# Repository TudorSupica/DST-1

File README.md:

# The [BOSS DS-1](https://www.thomann.de/ro/boss_ds1_distortion.htm)

Maybe the most popular distortion pedal to ever hit the market. It's harsh attack and heavy distortion make it the perfect choice for genres like thrash and heavy metal.

# The [DST-1](https://github.com/TudorSupica/DST-1/)

The DST-1 is a copy of the DS-1's schematic, but modified in certain ways.
The original DS-1 used some relatively hard to find components, so i've swapped those out with some common components like the 2N3904 and the TL072.

This distorion pedal is intended to set the standard to me as to what "a good distortion pedal" sounds like. Usually distortion pedals are quite cheap and easy to build, but their sound comes down to the components used. Thus, I might swap out the TL072 for other op-amps aswell as the transistors. Good components make good pedals, but sometimes their cheapness and imperfections make the pedal unique. 

# [The Schematic](https://github.com/TudorSupica/DST-1/blob/main/Schematic/)

The schematic is quite cramped since I wanted it to fit all in a single unbroken signal line, from the input to the output. The +Vcc and -Vcc are supplied using a voltage divider between the positive and negative terminals of a 9v battery, also forming a vitual ground. To make sure I make the disctinction between the Gnd of the battery and the Gnd of the signal, I decided to rename signal's ground to +4,5v since it's the midway point between the +9v and the 0v of the battery.

The 3PDT switch didn't had any symbol in KiCAD's library so I made them myself, aswell as the footprint, using the datasheet for the switch. Feel free to copy use and share since resources should not be kept behind paywalls and such and anybody should have the right to use resources to create / recreate things.

# [The PCB](https://github.com/TudorSupica/DST-1/blob/main/PCB/)
I've yet to test the circuit, but the PCB is on it's way and will soonly arrive.

The PCB is made to fit in a Hammond 1590B aluminium enclosure, thus it's rather strict dimensions. I'm not quite sure if it'll fit tho since I've been too lazy to make the board's outline match the enclosure's lid, but I plan to do it... sometime in the future I hope ...

Here is the datasheet for the enclosure tho!

I also added some (4 to be precise) M3 mounting holes that are connected directly to 0v, thus being capable to ground the whole PCB if the user so desires.
The LED can be anything from red to UV, I used a 220 ohm resistor but it can be replaced with any kind of THT resistor to match the desired brightness/current need of an LED, if so desired.

I plan to power up the pedal using a 9v battery connected via a barrel jack, at the back of the board. 

To do:
- [x] Schematic
- [x] PCB design
- [ ] Integrate the pedal in an enclosure

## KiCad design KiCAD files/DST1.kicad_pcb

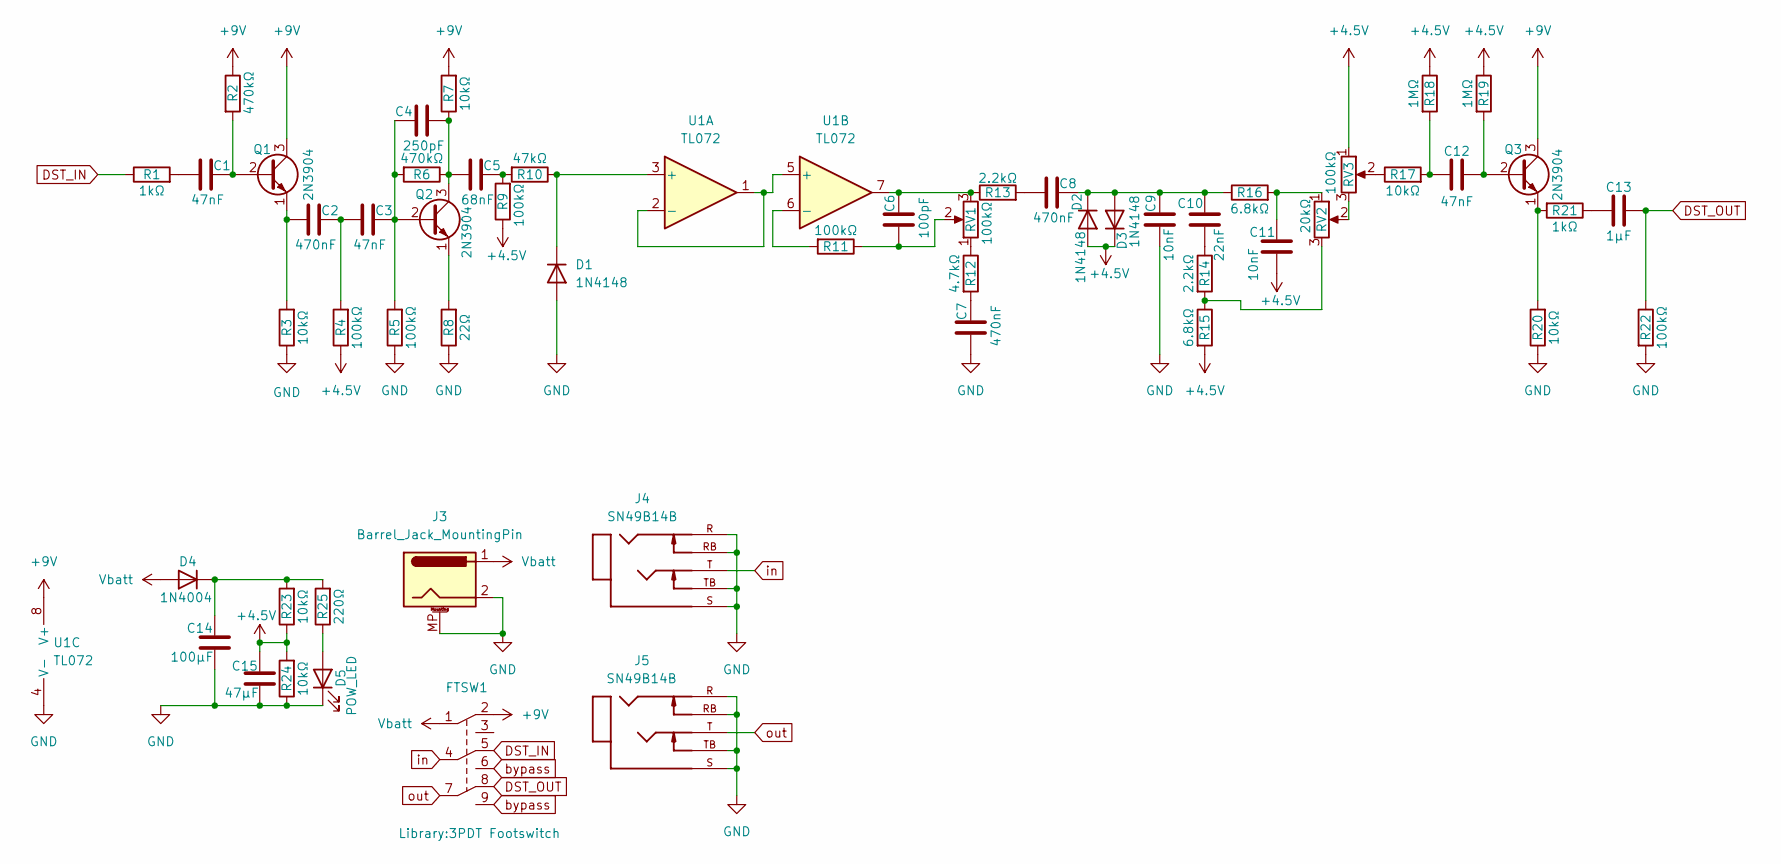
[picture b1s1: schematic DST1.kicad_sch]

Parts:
C1, C3, C12: 47nF; C_Rect_L4.6mm_W3.0mm_P2.50mm_MKS02_FKP02
C2, C7, C8: 470nF; C_Rect_L4.6mm_W3.0mm_P2.50mm_MKS02_FKP02
C4: 250pF; C_Rect_L4.6mm_W3.0mm_P2.50mm_MKS02_FKP02
C5: 68nF; C_Rect_L4.6mm_W3.0mm_P2.50mm_MKS02_FKP02
C6: 100pF; C_Rect_L4.6mm_W3.0mm_P2.50mm_MKS02_FKP02
C9, C11: 10nF; C_Rect_L4.6mm_W3.0mm_P2.50mm_MKS02_FKP02
C10: 22nF; C_Rect_L4.6mm_W3.0mm_P2.50mm_MKS02_FKP02
C13: 1µF; C_Rect_L4.6mm_W3.0mm_P2.50mm_MKS02_FKP02
C14: 100µF; C_Radial_D4.0mm_H5.0mm_P1.50mm
C15: 47µF; C_Radial_D4.0mm_H5.0mm_P1.50mm
D1, D2, D3: 1N4148; D_DO-35_SOD27_P7.62mm_Horizontal
D4: 1N4004; D_DO-41_SOD81_P10.16mm_Horizontal
D5: POW_LED; LED_D5.0mm
FTSW1: 3PDT Footswitch
J3: Barrel_Jack_MountingPin; BarrelJack_Kycon_KLDX-0202-xC_Horizontal
J4, J5: SN49B14B; PJ-644C; PARTREV F
Q1, Q2, Q3: 2N3904; TO-92
R1, R21: 1kΩ; R_Axial_DIN0207_L6.3mm_D2.5mm_P10.16mm_Horizontal
R2, R6: 470kΩ; R_Axial_DIN0207_L6.3mm_D2.5mm_P10.16mm_Horizontal
R3, R7, R17, R20, R23, R24: 10kΩ; R_Axial_DIN0207_L6.3mm_D2.5mm_P10.16mm_Horizontal
R4, R5, R9, R11, R22: 100kΩ; R_Axial_DIN0207_L6.3mm_D2.5mm_P10.16mm_Horizontal
R8: 22Ω; R_Axial_DIN0207_L6.3mm_D2.5mm_P10.16mm_Horizontal
R10: 47kΩ; R_Axial_DIN0207_L6.3mm_D2.5mm_P10.16mm_Horizontal
R12: 4.7kΩ; R_Axial_DIN0207_L6.3mm_D2.5mm_P10.16mm_Horizontal
R13, R14: 2.2kΩ; R_Axial_DIN0207_L6.3mm_D2.5mm_P10.16mm_Horizontal
R15, R16: 6.8kΩ; R_Axial_DIN0207_L6.3mm_D2.5mm_P10.16mm_Horizontal
R18, R19: 1MΩ; R_Axial_DIN0207_L6.3mm_D2.5mm_P10.16mm_Horizontal
R25: 220Ω; R_Axial_DIN0207_L6.3mm_D2.5mm_P10.16mm_Horizontal
RV1, RV3: 100kΩ; Potentiometer_Alpha_RD901F-40-00D_Single_Vertical
RV2: 20kΩ; Potentiometer_Alpha_RD901F-40-00D_Single_Vertical
U1: TL072; DIP-8_W7.62mm

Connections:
+4.5V: C11.1, C15.1, D2.2 (A), D3.1 (K), R4.1, R9.1, R15.2, R18.1, R19.1, R23.1, R24.2, RV3.1
+9V: FTSW1.2, Q1.3 (C), Q3.3 (C), R2.1, R7.2, U1.8 (V+)
DST_IN: FTSW1.5, R1.1
DST_OUT: C13.1, FTSW1.8, R22.1
GND: C7.1, C9.1, C14.2, C15.2, D1.2 (A), D5.1 (K), J3.2, J3.3, J3.MP (MountPin), J4.R, J4.RB, J4.S, J4.SB, J4.TB, J5.R, J5.RB, J5.S, J5.SB, J5.TB, R3.1, R5.1, R8.1, R20.1, R22.2, R24.1, U1.4 (V-)
unnamed: C1.1, R1.2
unnamed: C2.2, C3.1, R4.2
unnamed: C5.2, R9.2, R10.2
unnamed: C6.1, R11.1, RV1.2
unnamed: C6.2, R13.1, RV1.3, U1.7
unnamed: C7.2, R12.2
unnamed: C8.1, R13.2
unnamed: C10.1, R14.1
unnamed: C11.2, R16.2, RV2.1
unnamed: C12.2, R17.2, R18.2
unnamed: C13.2, R21.1
unnamed: D1.1 (K), R10.1, U1.3 (+)
unnamed: C8.2, C9.2, C10.2, D2.1 (K), D3.2 (A), R16.1
unnamed: C14.1, D4.1 (K), R23.2, R25.2
unnamed: D5.2 (A), R25.1
unnamed: C1.2, Q1.2 (B), R2.2
unnamed: C2.1, Q1.1 (E), R3.2
unnamed: C3.2, C4.1, Q2.2 (B), R5.2, R6.2
unnamed: C4.2, C5.1, Q2.3 (C), R6.1, R7.1
unnamed: Q2.1 (E), R8.2
unnamed: C12.1, Q3.2 (B), R19.2
unnamed: Q3.1 (E), R20.2, R21.2
unnamed: R12.1, RV1.1
unnamed: R14.2, R15.1, RV2.3
unnamed: R17.1, RV3.2
unnamed: RV2.2, RV3.3
unnamed: U1.1, U1.2 (-), U1.5 (+)
unnamed: R11.2, U1.6 (-)
Vbatt: D4.2 (A), FTSW1.1, J3.1
bypass: FTSW1.6, FTSW1.9
in: FTSW1.4, J4.T
out: FTSW1.7, J5.T

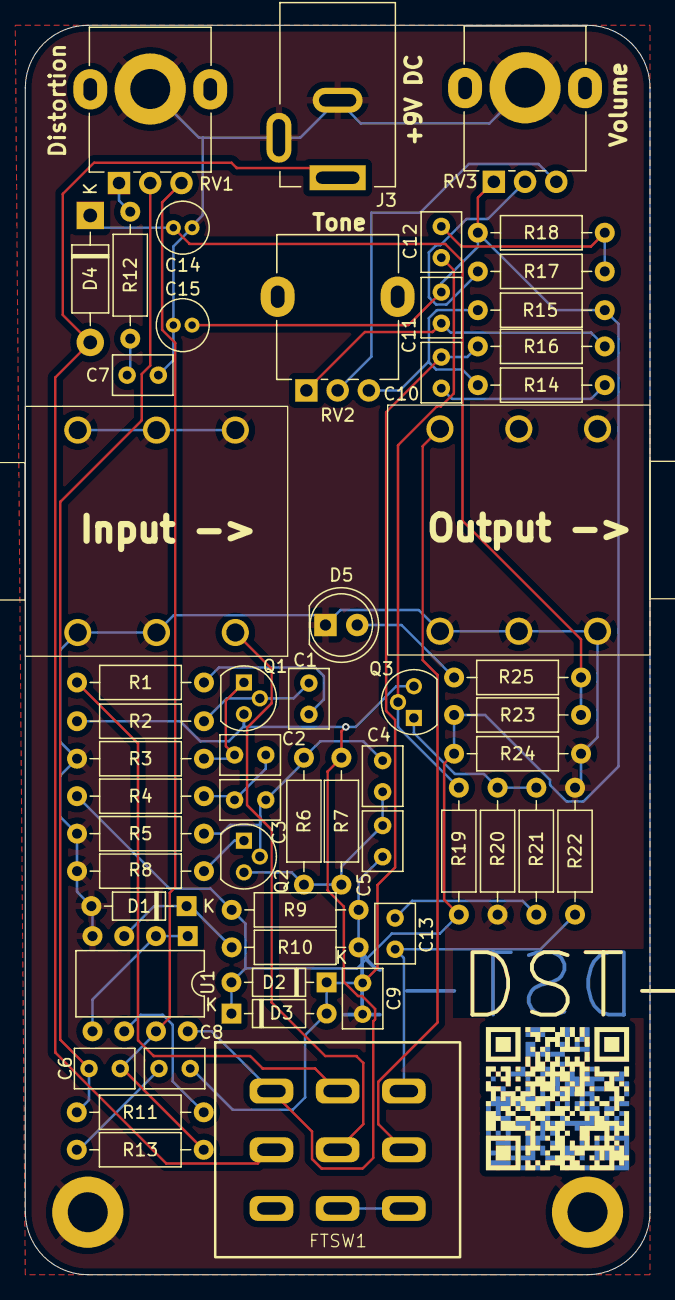
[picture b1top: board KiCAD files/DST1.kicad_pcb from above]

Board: 2 copper layers, 50.0 x 100.0 mm, 56 parts (0 on the bottom side), 37 nets.

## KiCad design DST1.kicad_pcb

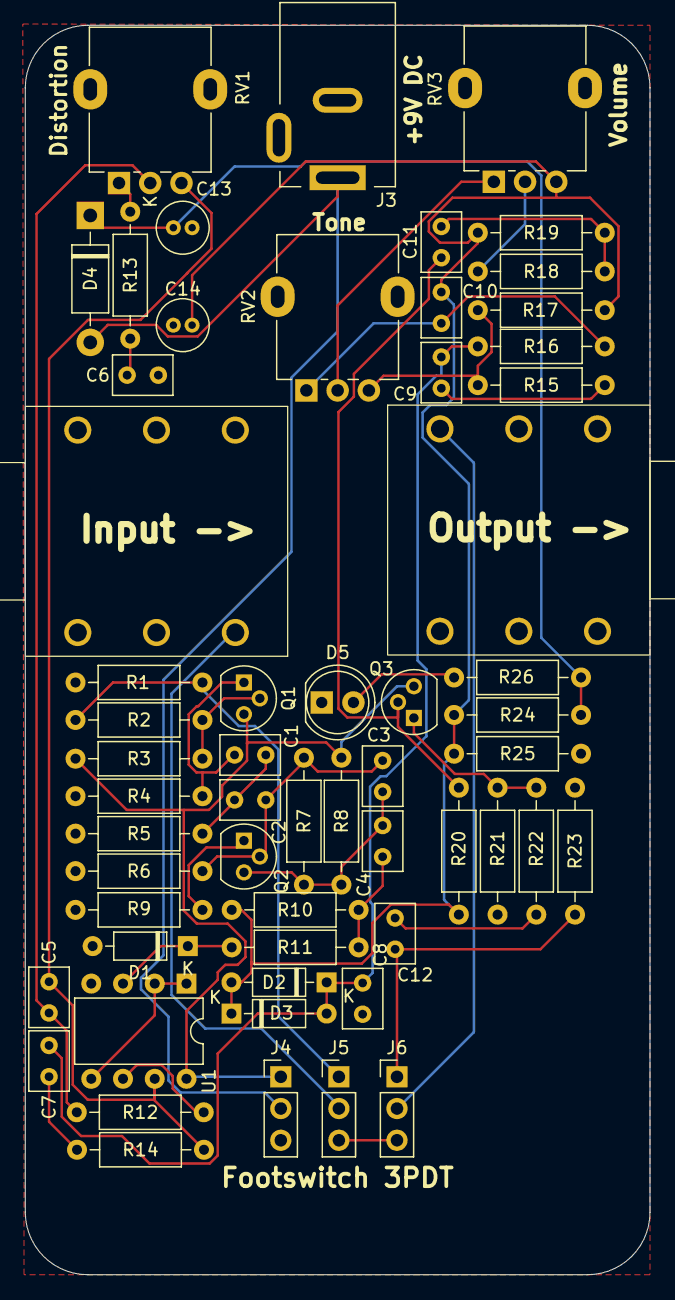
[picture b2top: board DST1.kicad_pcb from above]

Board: 2 copper layers, 50.0 x 100.0 mm, 58 parts (0 on the bottom side), 36 nets.

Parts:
C1, C6, C7: 470nF; C_Rect_L4.6mm_W3.0mm_P2.50mm_MKS02_FKP02
C2, C11: 47nF; C_Rect_L4.6mm_W3.0mm_P2.50mm_MKS02_FKP02
C3: 250pF; C_Rect_L4.6mm_W3.0mm_P2.50mm_MKS02_FKP02
C4: 68nF; C_Rect_L4.6mm_W3.0mm_P2.50mm_MKS02_FKP02
C5, C8, C9, C10: 100pF; C_Rect_L4.6mm_W3.0mm_P2.50mm_MKS02_FKP02
C12: 1µF; C_Rect_L4.6mm_W3.0mm_P2.50mm_MKS02_FKP02
C13: 100µF; C_Radial_D4.0mm_H5.0mm_P1.50mm
C14: 47µF; C_Radial_D4.0mm_H5.0mm_P1.50mm
D1, D2, D3: 1N4148; D_DO-35_SOD27_P7.62mm_Horizontal
D4: 1N4004; D_DO-41_SOD81_P10.16mm_Horizontal
D5: POW_LED; LED_D5.0mm
J1, J2: SN49B14B; PJ-644C
J3: Barrel_Jack_MountingPin; BarrelJack_Kycon_KLDX-0202-xC_Horizontal
J4, J5, J6: Conn_01x03_Pin; PinHeader_1x03_P2.54mm_Vertical
Q1, Q2, Q3: 2N3904; TO-92
R1, R19, R20: 1MΩ; R_Axial_DIN0207_L6.3mm_D2.5mm_P10.16mm_Horizontal
R2, R22: 1kΩ; R_Axial_DIN0207_L6.3mm_D2.5mm_P10.16mm_Horizontal
R3, R7: 470kΩ; R_Axial_DIN0207_L6.3mm_D2.5mm_P10.16mm_Horizontal
R4, R8, R18, R21, R24, R25: 10kΩ; R_Axial_DIN0207_L6.3mm_D2.5mm_P10.16mm_Horizontal
R5, R6, R10, R12, R23: 100kΩ; R_Axial_DIN0207_L6.3mm_D2.5mm_P10.16mm_Horizontal
R9: 22Ω; R_Axial_DIN0207_L6.3mm_D2.5mm_P10.16mm_Horizontal
R11: 47kΩ; R_Axial_DIN0207_L6.3mm_D2.5mm_P10.16mm_Horizontal
R13: 4.7kΩ; R_Axial_DIN0207_L6.3mm_D2.5mm_P10.16mm_Horizontal
R14, R15, R17: 2.2kΩ; R_Axial_DIN0207_L6.3mm_D2.5mm_P10.16mm_Horizontal
R16: 6.8kΩ; R_Axial_DIN0207_L6.3mm_D2.5mm_P10.16mm_Horizontal
R26: 220Ω; R_Axial_DIN0207_L6.3mm_D2.5mm_P10.16mm_Horizontal
RV1: 100kΩ; Potentiometer_Alpha_RD901F-40-00D_Single_Vertical
RV2, RV3: 20kΩ; Potentiometer_Alpha_RD901F-40-00D_Single_Vertical
U1: TL072; DIP-8_W7.62mm

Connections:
+4.5V: C10.1, C14.1, D2.2 (A), D3.1 (K), R10.1, R17.2, R19.1, R20.1, R24.1, R25.2, RV3.3
+9V: J4.1, Q1.3 (C), Q3.3 (C), R3.1, R8.2, U1.8 (V+)
GND: C6.1, C8.1, C13.2, C14.2, D1.2 (A), D5.1 (K), J1.R, J1.RB, J1.S, J1.TB, J2.R, J2.RB, J2.S, J2.TB, J3.2, R1.2, R4.1, R5.1, R6.1, R9.1, R21.1, R23.2, R25.1, U1.4 (V-)
unnamed: C1.2, C2.1, R5.2
unnamed: C4.2, R10.2, R11.2
unnamed: C5.1, R12.1, RV1.2
unnamed: C5.2, R14.1, RV1.3, U1.7
unnamed: C6.2, R13.2
unnamed: C7.1, R14.2
unnamed: C9.1, R15.1
unnamed: C10.2, R16.2, RV2.1
unnamed: C11.2, R18.2, R19.2
unnamed: C12.2, R22.1
unnamed: D1.1 (K), R11.1, U1.3 (+)
unnamed: C7.2, C8.2, C9.2, D2.1 (K), D3.2 (A), R16.1
unnamed: C13.1, D4.1 (K), R24.2, R26.2
unnamed: D5.2 (A), R26.1
unnamed: J5.1, R1.1, R2.1
unnamed: C12.1, J6.1, R23.1
unnamed: Q1.2 (B), R2.2, R3.2
unnamed: C1.1, Q1.1 (E), R4.2
unnamed: C2.2, C3.1, Q2.2 (B), R6.2, R7.2
unnamed: C3.2, C4.1, Q2.3 (C), R7.1, R8.1
unnamed: Q2.1 (E), R9.2
unnamed: C11.1, Q3.2 (B), R20.2
unnamed: Q3.1 (E), R21.2, R22.2
unnamed: R13.1, RV1.1
unnamed: R15.2, R17.1, RV2.3
unnamed: R18.1, RV3.2
unnamed: RV2.2, RV3.1
unnamed: U1.1, U1.2 (-), U1.5 (+)
unnamed: R12.2, U1.6 (-)
Vbatt: D4.2 (A), J3.1
bypass: J5.3, J6.3
in: J1.T, J5.2
out: J2.T, J6.2

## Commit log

2024-07-16 Added the PCB design and the schematic
2024-07-16 Added a new 3D image of the PCB
2024-07-16 Changed the folders around a bit
2024-07-16 moved the project file
2024-11-19 Update
    I updated the schematic and finished the PCB, might need to upload new photos tho.
2024-12-01 Update
    I updated the schematic PDF and the photo renders of the board
2024-12-18 Updated schematic and PCB
    I chose the wrong values for some resistors and capacitors, and so I had to update the schematic. I also wired the footswitch in a wrong manner and so I had to update the PCB.
2025-01-13 Updated the PCB
2025-01-13 Added gerber files
